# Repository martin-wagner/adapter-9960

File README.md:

# adapter-9960
Adapter for unobtainable nixie tube driver IC fairchild 9960 ( 960, 996079 ) to SN74414 / K155id1

Contains Kicad project, pdf schematic and gerber files for ordering at your pcb service of choise. Added some other more or less useful stuff to the panel to optimeze for the common 10x10cm pcb manufacturing services. Should fit as direct replacement if pcb is not too densly packed.

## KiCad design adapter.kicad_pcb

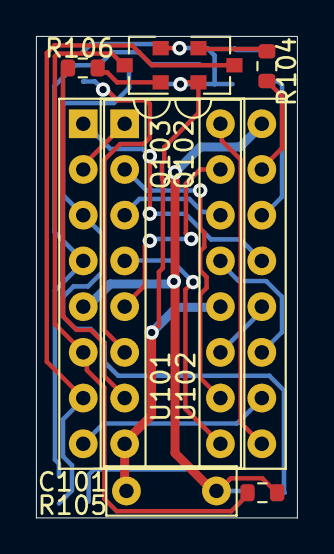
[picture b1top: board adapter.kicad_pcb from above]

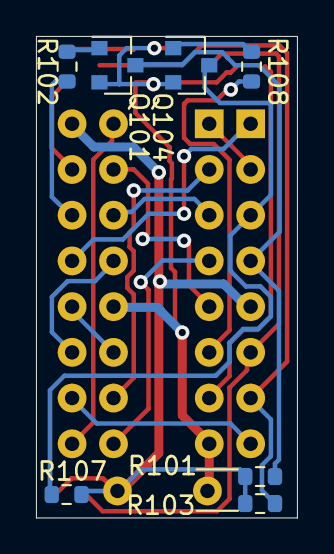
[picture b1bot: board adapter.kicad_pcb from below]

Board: 2 copper layers, 14.5 x 26.8 mm, 15 parts (7 on the bottom side), 24 nets.

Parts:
C101: 100n; C_Disc_D7.0mm_W2.5mm_P5.00mm
Q101, Q102, Q103, Q104: Q_NPN_BEC; SOT-23
R101, R102, R103, R104, R105, R106, R107, R108: 1k; R_0603_1608Metric
U101: 74141; DIP-16_W7.62mm_Socket
U102: fairchild_9960; DIP-16_W7.62mm_Socket

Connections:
+5V: C101.1, R101.2, R103.2, R105.2, R107.2, U101.5, U102.16
GND: C101.2, Q101.2, Q102.2, Q103.2, Q104.2, U101.12, U102.8
unnamed: Q101.1, R102.2
unnamed: Q101.3, R101.1, U101.4
unnamed: Q102.1, R104.2
unnamed: Q102.3, R103.1, U101.7
unnamed: Q103.1, R106.2
unnamed: Q103.3, R105.1, U101.6
unnamed: Q104.1, R108.2
unnamed: Q104.3, R107.1, U101.3
unnamed: R102.1, U102.14
unnamed: R104.1, U102.15
unnamed: R106.1, U102.7
unnamed: R108.1, U102.6
unnamed: U101.1, U102.13
unnamed: U101.2, U102.1
unnamed: U101.8, U102.10
unnamed: U101.9, U102.4
unnamed: U101.10, U102.2
unnamed: U101.11, U102.12
unnamed: U101.13, U102.11
unnamed: U101.14, U102.3
unnamed: U101.15, U102.5
unnamed: U101.16, U102.9

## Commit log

2021-08-01 Add: Kicad, pdf schematic, gerbers
